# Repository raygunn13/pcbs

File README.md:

pcbs
====

PCB Layouts and Libraries

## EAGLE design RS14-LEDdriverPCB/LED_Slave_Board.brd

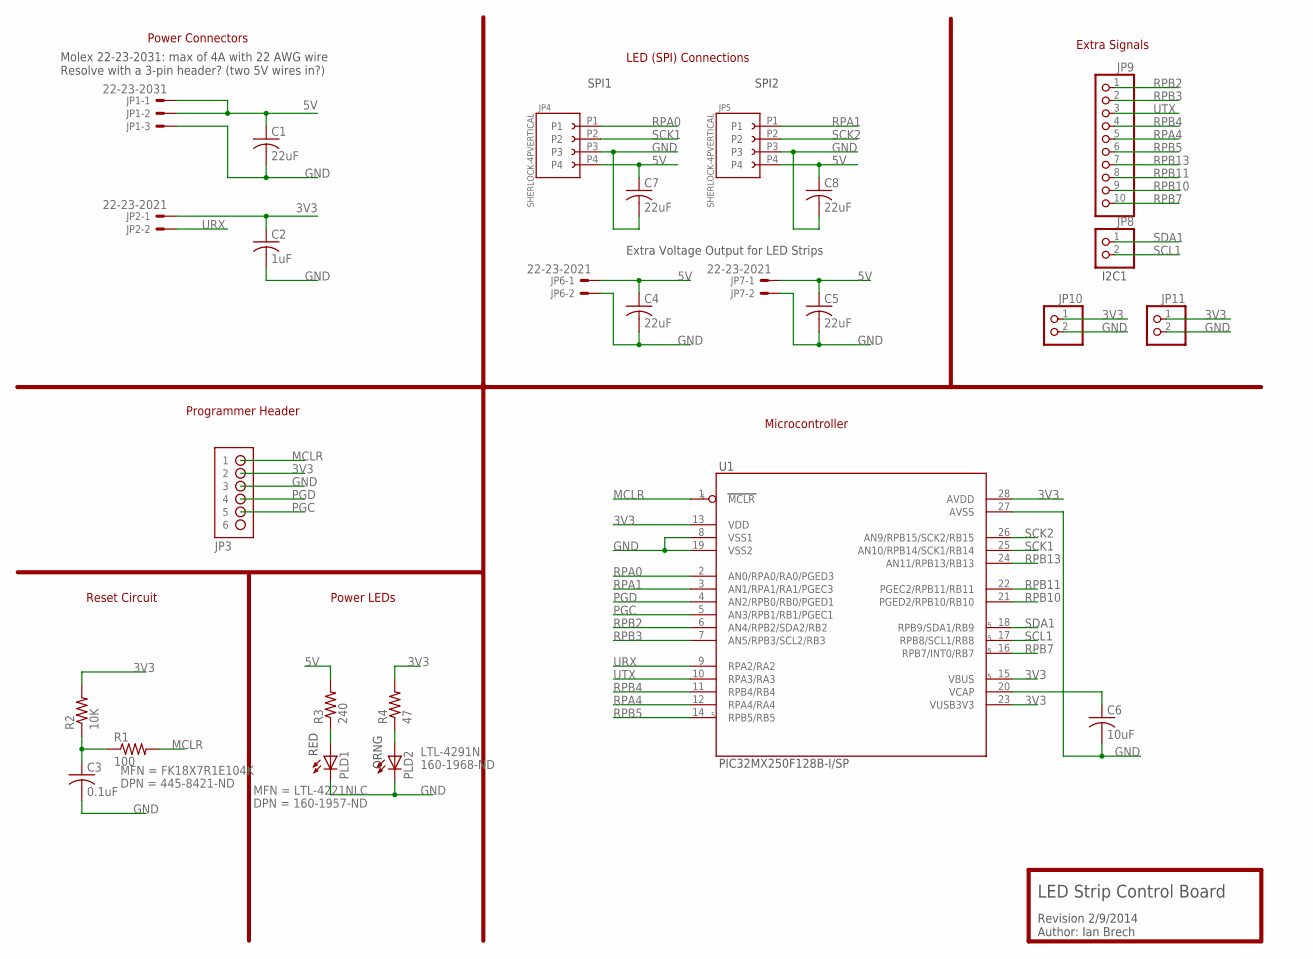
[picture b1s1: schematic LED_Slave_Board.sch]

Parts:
C1, C4, C5, C7, C8: 22uF; C050-045X075
C2: 1uF; C025-024X044
C3: 0.1uF; C025-040X050
C6: 10uF; C025-040X050
JP1: 22-23-2031
JP2, JP6, JP7: 22-23-2021
JP3: HDR-1X6-OFFSET; HDR-1X6_OFFSET
JP4, JP5: SHERLOCK-4PVERTICAL; 35362-04**
JP8, JP10, JP11: PINHD-1X2; 1X02
JP9: PINHD-1X10; 1X10
PLD1, PLD2: LED3MM
R1: 100; 0204/7
R2: 10K; 0204/7
R3: 240; 0204/7
R4: 47; 0204/7
U1: PIC32MX250F128B-I/SP; DIP254P762X508-28

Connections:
3V3: C2.1, JP2.1, JP3.2, JP10.1, JP11.1, R2.2, R4.2, U1.13 (VDD), U1.15 (VBUS), U1.23 (VUSB3V3), U1.28 (AVDD)
5V: C1.1, C4.1, C5.1, C7.1, C8.1, JP1.1, JP1.2, JP4.P4, JP5.P4, JP6.1, JP7.1, R3.2
GND: C1.2, C2.2, C3.2, C4.2, C5.2, C6.2, C7.2, C8.2, JP1.3, JP3.3, JP4.P3, JP5.P3, JP6.2, JP7.2, JP10.2, JP11.2, PLD1.K (C), PLD2.K (C), U1.8 (VSS1), U1.19 (VSS2), U1.27 (AVSS)
MCLR: JP3.1, R1.2, U1.1 (MCLR)
unnamed: PLD1.A, R3.1
unnamed: C3.1, R1.1, R2.1
unnamed: PLD2.A, R4.1
unnamed: C6.1, U1.20 (VCAP)
PGC: JP3.5, U1.5 (AN3/RPB1/RB1/PGEC1)
PGD: JP3.4, U1.4 (AN2/RPB0/RB0/PGED1)
RPA0: JP4.P1, U1.2 (AN0/RPA0/RA0/PGED3)
RPA1: JP5.P1, U1.3 (AN1/RPA1/RA1/PGEC3)
RPA4: JP9.5, U1.12 (RPA4/RA4)
RPB2: JP9.1, U1.6 (AN4/RPB2/SDA2/RB2)
RPB3: JP9.2, U1.7 (AN5/RPB3/SCL2/RB3)
RPB4: JP9.4, U1.11 (RPB4/RB4)
RPB5: JP9.6, U1.14 (RPB5/RB5)
RPB7: JP9.10, U1.16 (RPB7/INT0/RB7)
RPB10: JP9.9, U1.21 (PGED2/RPB10/RB10)
RPB11: JP9.8, U1.22 (PGEC2/RPB11/RB11)
RPB13: JP9.7, U1.24 (AN11/RPB13/RB13)
SCK1: JP4.P2, U1.25 (AN10/RPB14/SCK1/RB14)
SCK2: JP5.P2, U1.26 (AN9/RPB15/SCK2/RB15)
SCL1: JP8.2, U1.17 (RPB8/SCL1/RB8)
SDA1: JP8.1, U1.18 (RPB9/SDA1/RB9)
URX: JP2.2, U1.9 (RPA2/RA2)
UTX: JP9.3, U1.10 (RPA3/RA3)

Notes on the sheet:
Extra Signals
Revision 2/9/2014 Author: Ian Brech
SPI1
SPI2
Molex 22-23-2031: max of 4A with 22 AWG wire Resolve with a 3-pin header? (two 5V wires in?)
Programmer Header
I2C1
Extra Voltage Output for LED Strips
LED Strip Control Board
LED (SPI) Connections
Reset Circuit
Power LEDs
Microcontroller
Power Connectors
RED
ORNG

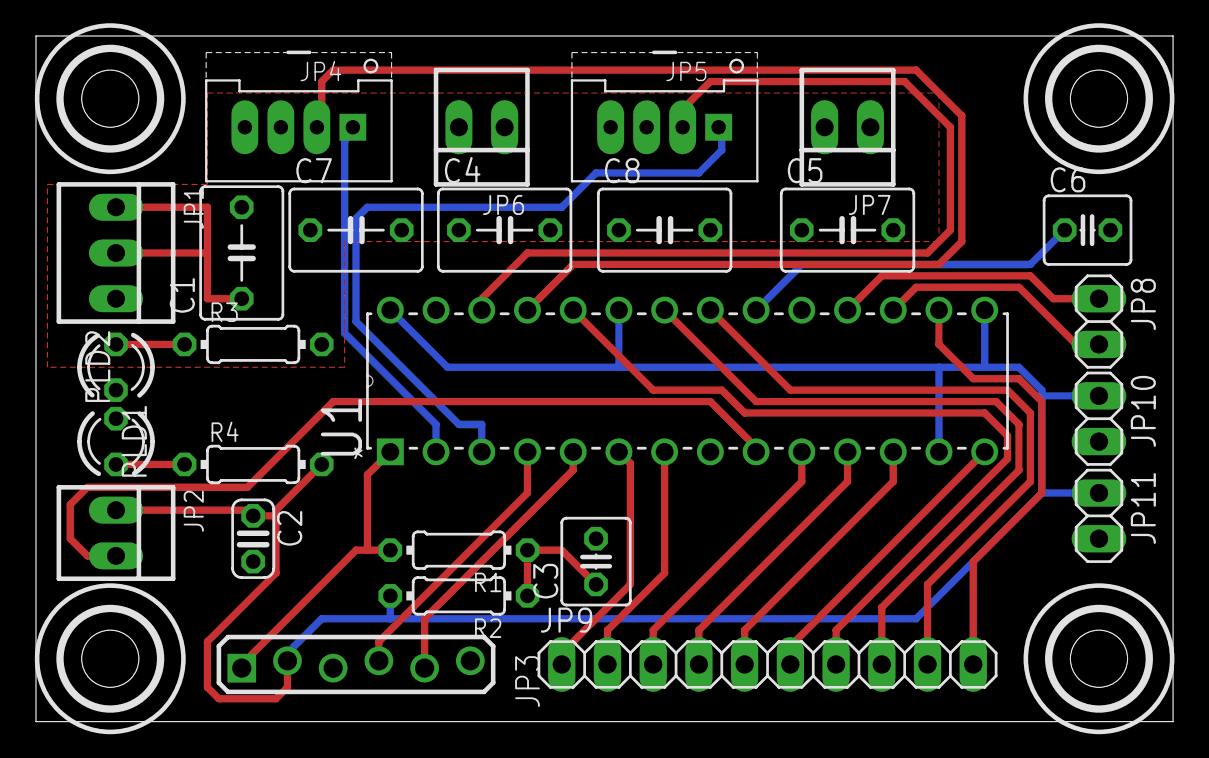
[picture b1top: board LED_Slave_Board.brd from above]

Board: 2 copper layers, 63.2 x 38.1 mm, 26 parts (0 on the bottom side), 27 nets.

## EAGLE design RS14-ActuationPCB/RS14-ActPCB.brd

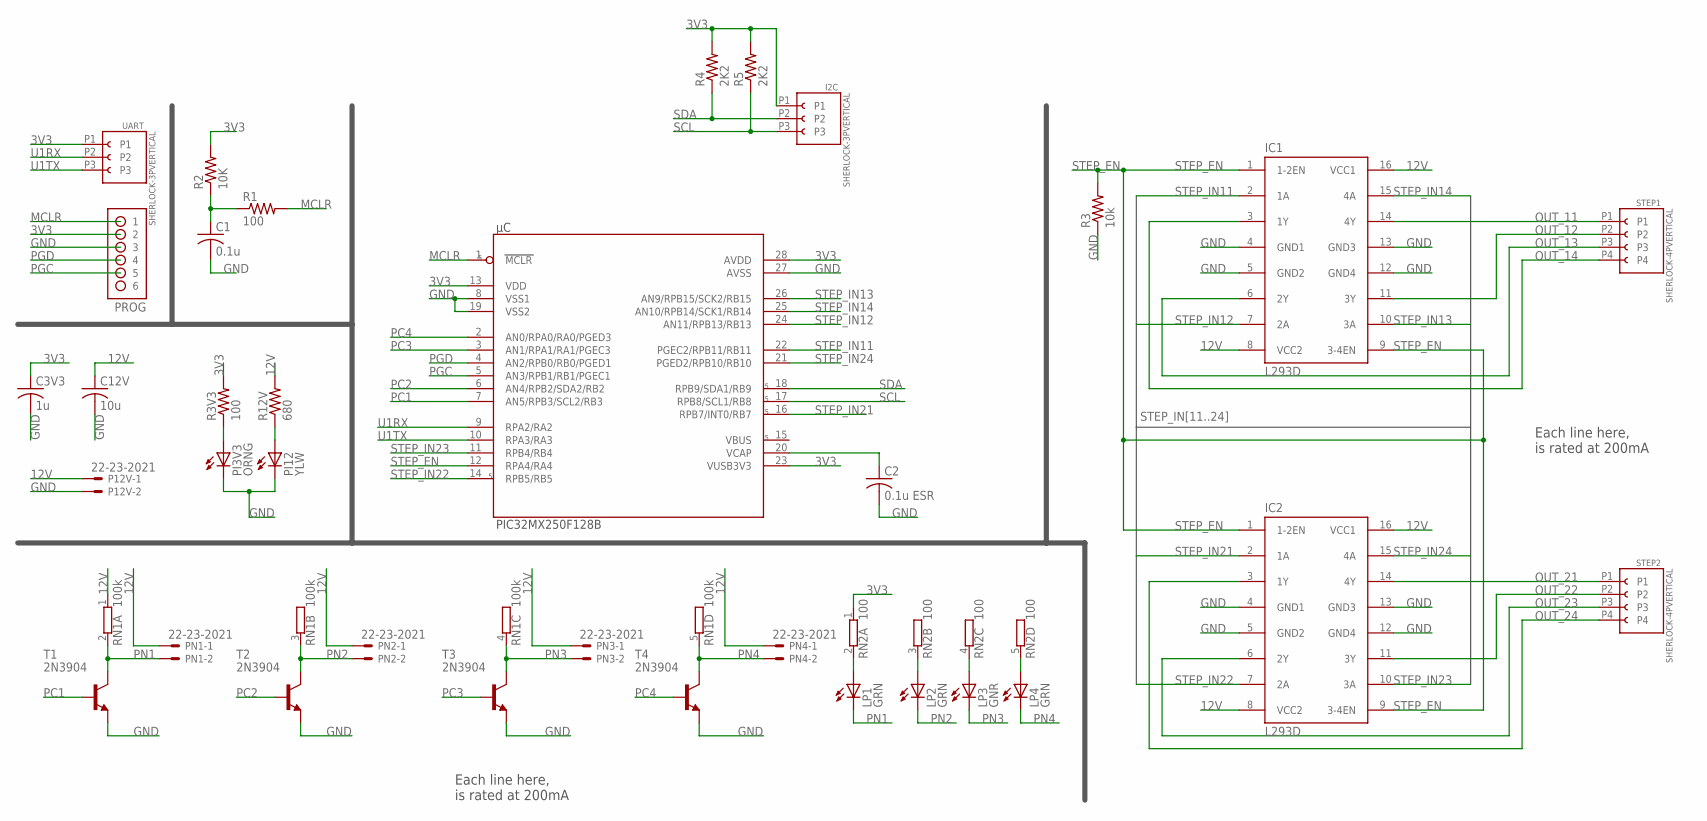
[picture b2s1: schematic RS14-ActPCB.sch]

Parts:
C1: 0.1u; C025-025X050
C2: 0.1u ESR; C025-025X050
C3V3: 1u; C025-025X050
C12V: 10u; C025-060X050
I2C: SHERLOCK-3PVERTICAL; 35362-03**
IC1, IC2: L293D; DIL16
LP1, LP2, LP4: GRN; LED3MM
LP3: GNR; LED3MM
P12V: 22-23-2021
PI3V3: ORNG; LED3MM
PI12: YLW; LED3MM
PN1, PN2, PN3, PN4: 22-23-2021
PROG: HDR-1X6-OFFSET; HDR-1X6_OFFSET
R1, R3V3: 100; 0204/7
R2: 10K; 0204/7
R3: 10k; 0204/7
R4, R5: 2K2; 0204/7
R12V: 680; 0204/7
RN1: 100k; SIL5
RN2: 100; SIL5
STEP1, STEP2: SHERLOCK-4PVERTICAL; 35362-04**
T1, T2, T3, T4: 2N3904; TO92
UART: SHERLOCK-3PVERTICAL; 35362-03**
µC: PIC32MX250F128B; DIP254P762X508-28

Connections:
3V3: C3V3.1, I2C.P1, PROG.2, R2.2, R3V3.2, R4.2, R5.2, RN2.1, UART.P1, µC.13 (VDD), µC.23 (VUSB3V3), µC.28 (AVDD)
12V: C12V.1, IC1.8 (VCC2), IC1.16 (VCC1), IC2.8 (VCC2), IC2.16 (VCC1), P12V.1, PN1.1, PN2.1, PN3.1, PN4.1, R12V.2, RN1.1
GND: C1.2, C2.2, C3V3.2, C12V.2, IC1.4 (GND1), IC1.5 (GND2), IC1.12 (GND4), IC1.13 (GND3), IC2.4 (GND1), IC2.5 (GND2), IC2.12 (GND4), IC2.13 (GND3), P12V.2, PI3V3.K (C), PI12.K (C), PROG.3, R3.1, T1.3 (E), T2.3 (E), T3.3 (E), T4.3 (E), µC.8 (VSS1), µC.19 (VSS2), µC.27 (AVSS)
MCLR: PROG.1, R1.2, µC.1 (MCLR)
unnamed: C2.1, µC.20 (VCAP)
unnamed: LP1.A, RN2.2
unnamed: PI12.A, R12V.1
unnamed: C1.1, R1.1, R2.1
unnamed: PI3V3.A, R3V3.1
unnamed: LP2.A, RN2.3 (2)
unnamed: LP3.A, RN2.4 (2)
unnamed: LP4.A, RN2.5 (2)
OUT_11: IC1.14 (4Y), STEP1.P1
OUT_12: IC1.11 (3Y), STEP1.P2
OUT_13: IC1.6 (2Y), STEP1.P3
OUT_14: IC1.3 (1Y), STEP1.P4
OUT_21: IC2.14 (4Y), STEP2.P1
OUT_22: IC2.11 (3Y), STEP2.P2
OUT_23: IC2.6 (2Y), STEP2.P3
OUT_24: IC2.3 (1Y), STEP2.P4
PC1: T1.2 (B), µC.7 (AN5/RPB3/SCL2/RB3)
PC2: T2.2 (B), µC.6 (AN4/RPB2/SDA2/RB2)
PC3: T3.2 (B), µC.3 (AN1/RPA1/RA1/PGEC3)
PC4: T4.2 (B), µC.2 (AN0/RPA0/RA0/PGED3)
PGC: PROG.5, µC.5 (AN3/RPB1/RB1/PGEC1)
PGD: PROG.4, µC.4 (AN2/RPB0/RB0/PGED1)
PN1: LP1.K (C), PN1.2, RN1.2, T1.1 (C)
PN2: LP2.K (C), PN2.2, RN1.3 (2), T2.1 (C)
PN3: LP3.K (C), PN3.2, RN1.4 (2), T3.1 (C)
PN4: LP4.K (C), PN4.2, RN1.5 (2), T4.1 (C)
SCL: I2C.P3, R5.1, µC.17 (RPB8/SCL1/RB8)
SDA: I2C.P2, R4.1, µC.18 (RPB9/SDA1/RB9)
STEP_EN: IC1.1 (1-2EN), IC1.9 (3-4EN), IC2.1 (1-2EN), IC2.9 (3-4EN), R3.2, µC.12 (RPA4/RA4)
STEP_IN11: IC1.2 (1A), µC.22 (PGEC2/RPB11/RB11)
STEP_IN12: IC1.7 (2A), µC.24 (AN11/RPB13/RB13)
STEP_IN13: IC1.10 (3A), µC.26 (AN9/RPB15/SCK2/RB15)
STEP_IN14: IC1.15 (4A), µC.25 (AN10/RPB14/SCK1/RB14)
STEP_IN21: IC2.2 (1A), µC.16 (RPB7/INT0/RB7)
STEP_IN22: IC2.7 (2A), µC.14 (RPB5/RB5)
STEP_IN23: IC2.10 (3A), µC.11 (RPB4/RB4)
STEP_IN24: IC2.15 (4A), µC.21 (PGED2/RPB10/RB10)
U1RX: UART.P2, µC.9 (RPA2/RA2)
U1TX: UART.P3, µC.10 (RPA3/RA3)

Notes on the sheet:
Each line here, is rated at 200mA

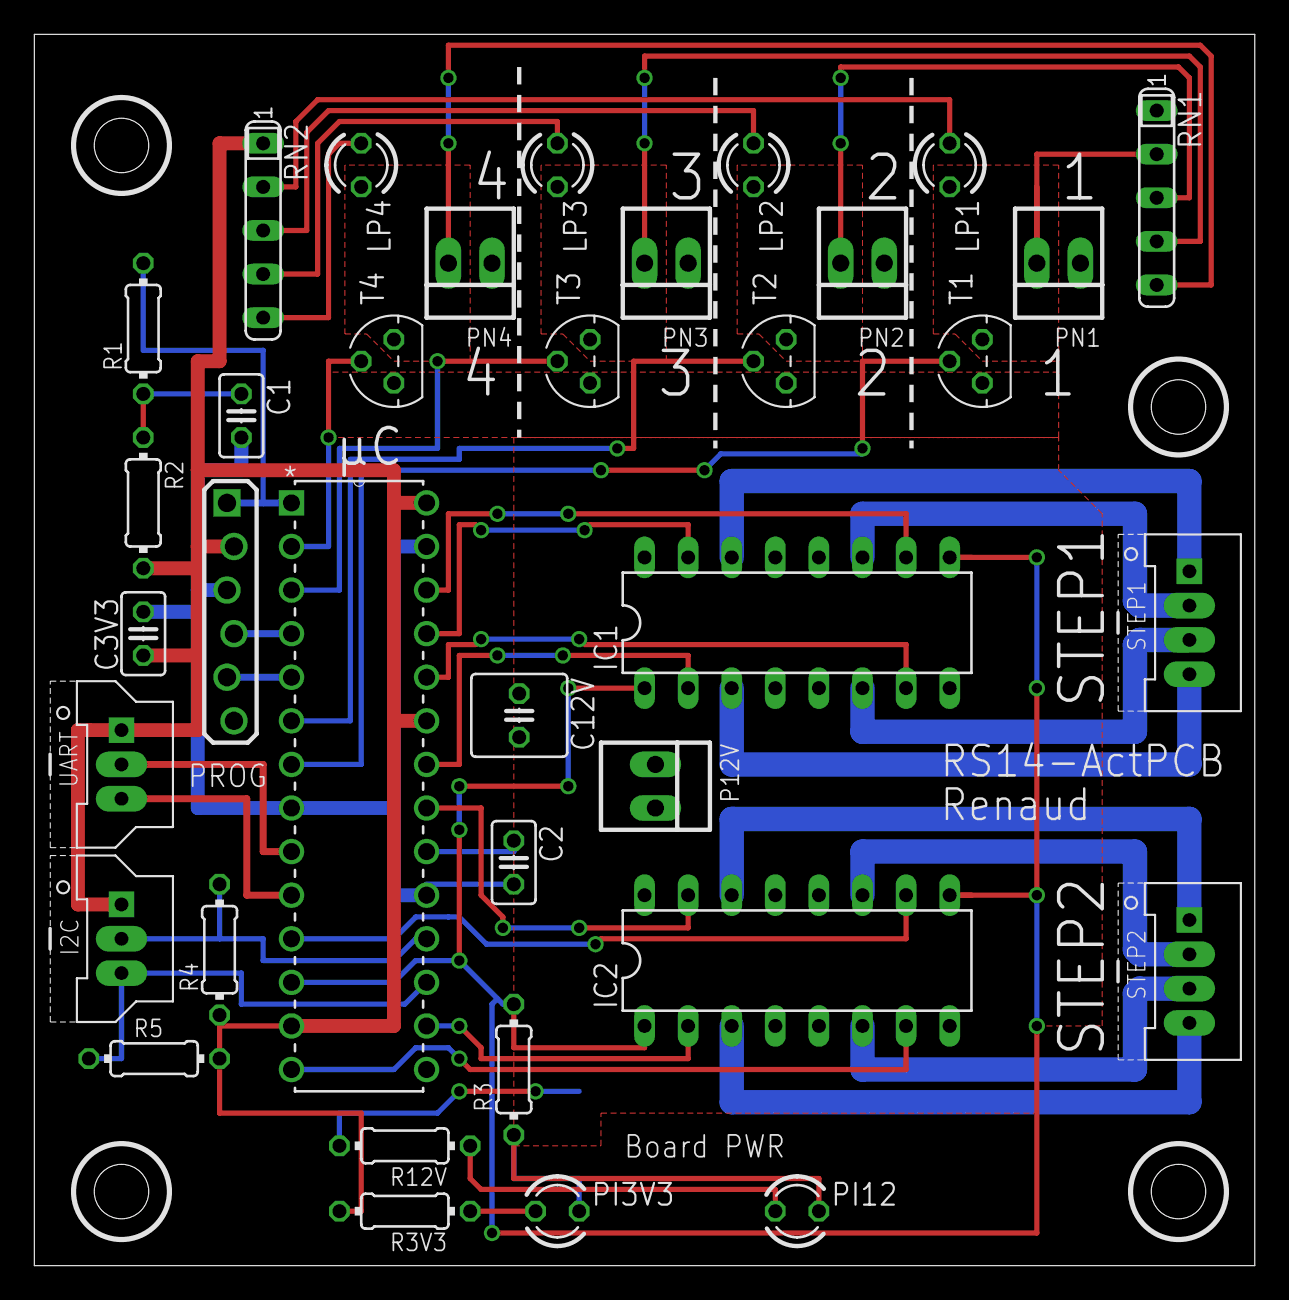
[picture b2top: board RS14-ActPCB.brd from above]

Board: 2 copper layers, 71.1 x 71.8 mm, 36 parts (0 on the bottom side), 43 nets.

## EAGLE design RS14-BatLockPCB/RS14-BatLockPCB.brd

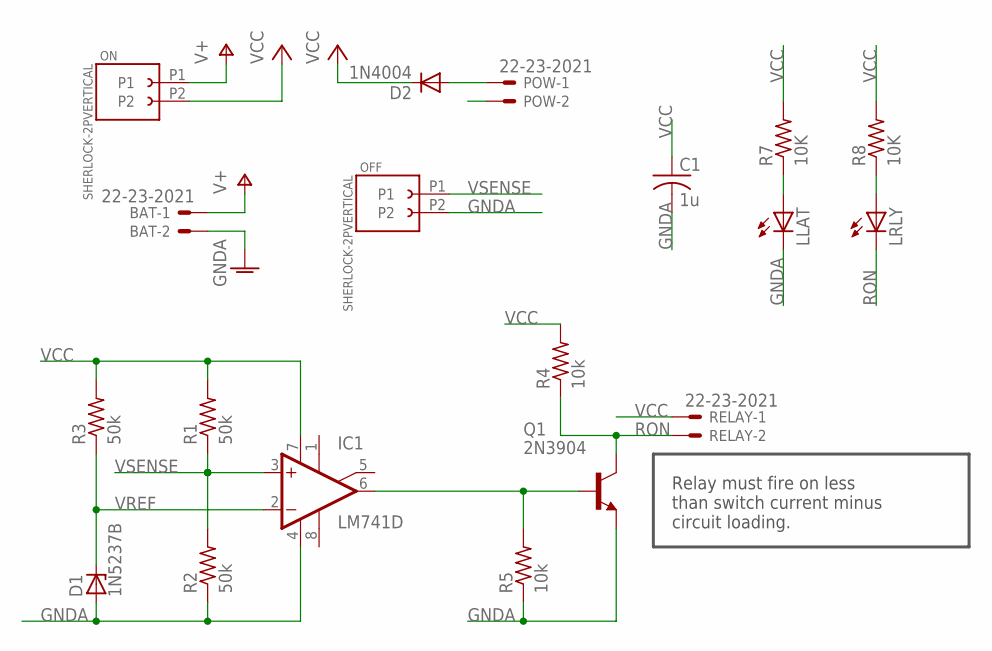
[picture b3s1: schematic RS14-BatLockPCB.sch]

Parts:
BAT: 22-23-2021
C1: 1u; C025-025X050
D1: 1N5237B; DO35Z10
D2: 1N4004; DO41-10
IC1: LM741D; SO08
LLAT: LED3MM
LRLY: LED3MM
OFF: SHERLOCK-2PVERTICAL; 35362-02**
ON: SHERLOCK-2PVERTICAL; 35362-02**
POW: 22-23-2021
Q1: 2N3904; TO92
R1, R2, R3: 50k; 0204/7
R4, R5: 10k; 0204/7
R7, R8: 10K; 0204/7
RELAY: 22-23-2021

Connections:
GNDA: BAT.2, C1.2, D1.A, IC1.4 (V-), LLAT.K (C), OFF.P2, Q1.3 (E), R2.1, R5.1
unnamed: IC1.6 (OUT), Q1.2 (B), R5.2
unnamed: D2.A, POW.1
unnamed: LLAT.A, R7.1
unnamed: LRLY.A, R8.1
RON: LRLY.K (C), Q1.1 (C), R4.1, RELAY.2
V+: BAT.1, ON.P1
VCC: C1.1, D2.C, IC1.7 (V+), ON.P2, R1.2, R3.2, R4.2, R7.2, R8.2, RELAY.1
VREF: D1.C, IC1.2 (-IN), R3.1
VSENSE: IC1.3 (+IN), OFF.P1, R1.1, R2.2

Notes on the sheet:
Relay must fire on less than switch current minus circuit loading.

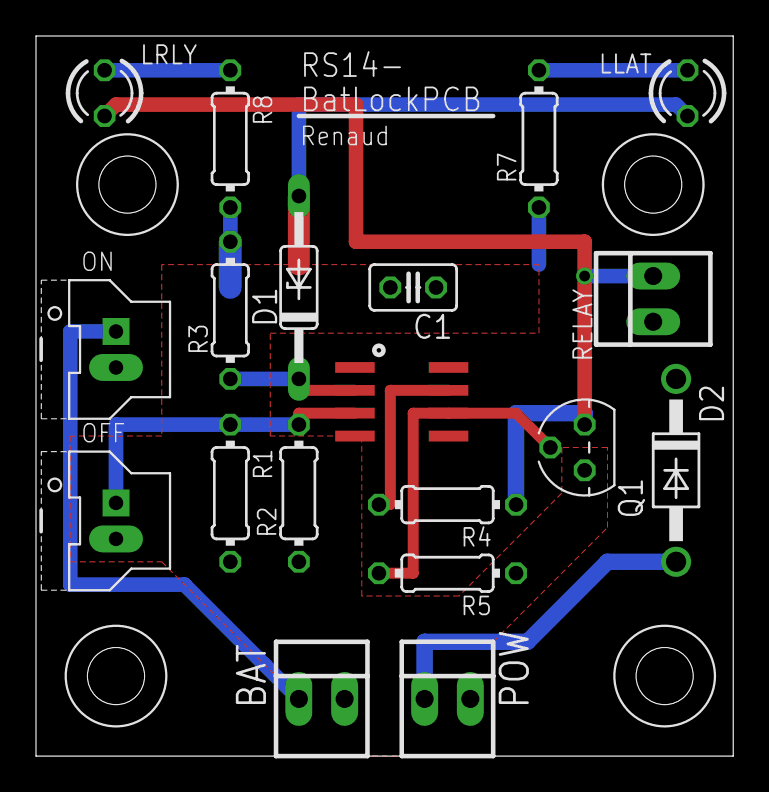
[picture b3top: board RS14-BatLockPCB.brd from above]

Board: 2 copper layers, 38.7 x 40.0 mm, 19 parts (0 on the bottom side), 10 nets.

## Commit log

2014-02-08 Inital commit. Contains libraries and manufacturing files we'll need for development.
2014-02-08 First revision of PCB Actuation board layout.
2014-02-08 Updated Actuation PCB
    This is the first draft layout.
    It only has two of the four desired screw holes, but this is mainly due
    to my refusal to make the board bigger in my tired stubbornness. There
    is also no labeling on the board (other than small built in markers) as
    of yet. So this will need to be added as well.
2014-02-08 Updated molex sherlock libraries
    This should produce fewer errors int he overall DRC block. An error titled "layer abuse" is expected, as it assumes that we do not want to put anything into the pad layer manually. This update furthe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
2014-02-08 Updated ActPCB with mounting holes and labels
    This includes larger print labels next to each pneumatic to identify which number of the pneumatic is being used, as well as large pring STEP1 and STEP2 next to each header to make them more visible.
2014-02-08 Quick DRC fix with board area.
2014-02-09 Battery Lockout PCB Added
    This commit adds the current version of the Battery Lockout/Power Controller PCB to our design. It also includes revisions to the main actuation PCB to change the LEDs to the 3mm convention we addopt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
2014-02-09 Updated libraries
    Updated libraries (hopefully for the last time) to make everything eagle happy.
2014-02-12 LED Driver Board
    Schematic and PCB layout for LED Driver Board
2014-02-12 Added eagle.epf
    Added eagle.epf
2014-02-12 Libraries for LED and Primary PCBs
    Eagle libraries used on the LED board and Primary Board, including the
    FTDI chip, optoisolators, and 3v3 power supply.
2014-02-12 Updated layouts for new hole sizes
    Updated both boards to include proper sized holes for the screws (correction from 0.22" radius to 0.22" diamater clearance). This also includes some minor tweeks to clean up the board size a bit.
2014-02-12 Revised Board and Schematic
    Changed capacitor footprints and screw hole placement
2014-02-12 Nathan
    Thruster_Feedback
